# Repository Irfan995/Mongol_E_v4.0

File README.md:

# Mongol_E_v4.0
This is MARS Rover Project of Team Interplanetar from Bangladesh University of Engineering and Technology.

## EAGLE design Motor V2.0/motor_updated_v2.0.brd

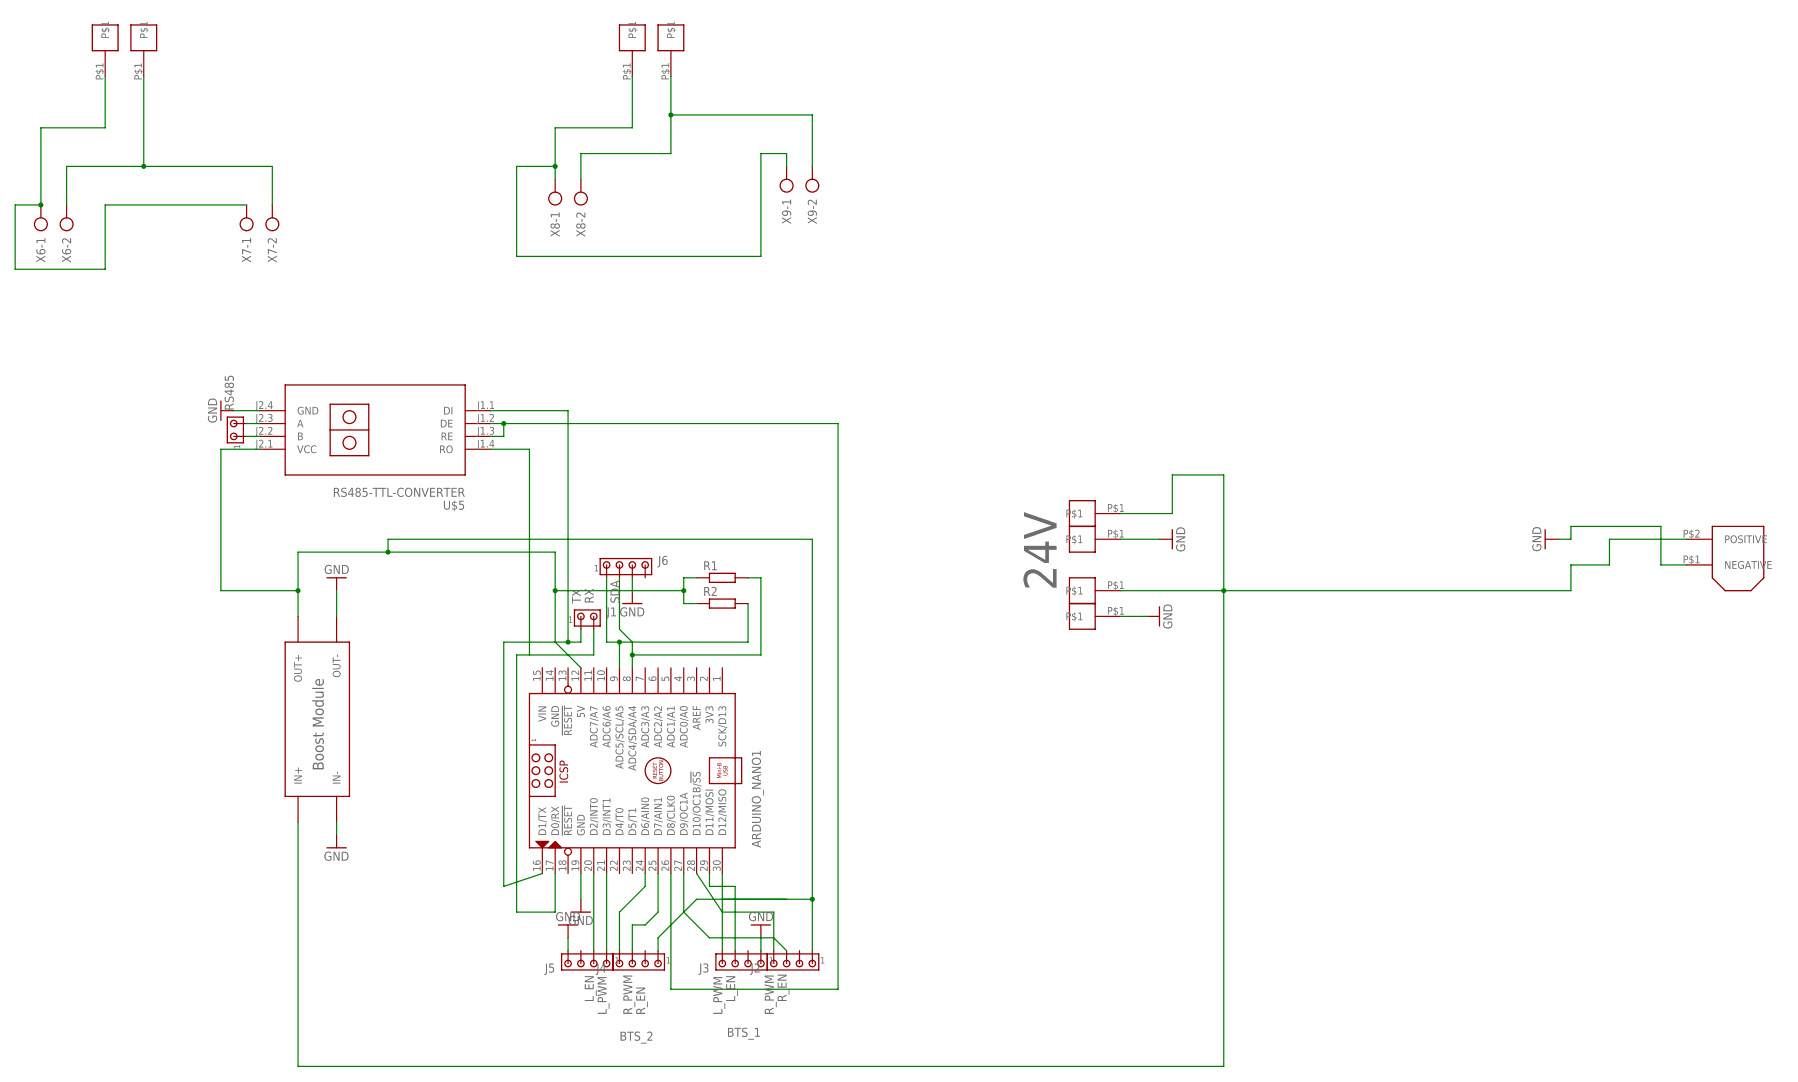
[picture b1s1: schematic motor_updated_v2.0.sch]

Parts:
ARDUINO_NANO1: ARDUINO_NANO
J1: MTA02-100; 10X02MTA
J2, J3, J4, J5, J6: MTA04-100; 10X04MTA
R1, R2: R-EU_0204/7; 0204/7
RS485: MTA02-100; 10X02MTA
U$4: BOOST_MODULE
U$5: RS485-TTL-CONVERTER
U$6, U$8, U$9, U$12, U$13, U$14, U$15, U$23: VIA
U$7: XT60; CONNECTOR
X6, X7, X8, X9: AK300/2

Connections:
GND: ARDUINO_NANO1.14 (GND), ARDUINO_NANO1.19 (GND), J3.1, J5.4, J6.3, U$4.IN-, U$4.OUT-, U$5.J2.4 (GND), U$6.P$1, U$7.P$1 (NEGATIVE), U$9.P$1
unnamed: ARDUINO_NANO1.12 (5V), J2.1, J4.1, R1.1, R2.1, U$4.OUT+, U$5.J2.1 (VCC)
unnamed: ARDUINO_NANO1.9 (ADC5/SCL/A5), J6.1, R2.2
unnamed: ARDUINO_NANO1.20 (D2/INT0), J5.2
unnamed: ARDUINO_NANO1.21 (D3/INT1), J5.1
unnamed: ARDUINO_NANO1.25 (D7/AIN1), J4.3
unnamed: ARDUINO_NANO1.24 (D6/AIN0), J4.4
unnamed: ARDUINO_NANO1.30 (D12/MISO), J3.4
unnamed: ARDUINO_NANO1.26 (D8/CLK0), U$5.J1.2 (DE), U$5.J1.3 (RE)
unnamed: U$4.IN+, U$7.P$2 (POSITIVE), U$8.P$1, U$23.P$1
unnamed: ARDUINO_NANO1.29 (D11/MOSI), J3.3
unnamed: RS485.2, U$5.J2.3 (A)
unnamed: RS485.1, U$5.J2.2 (B)
unnamed: ARDUINO_NANO1.28 (D10/OC1B/!SS), J2.4
unnamed: ARDUINO_NANO1.8 (ADC4/SDA/A4), J6.2, R1.2
unnamed: ARDUINO_NANO1.17 (D0/RX), J1.2, U$5.J1.4 (RO)
unnamed: ARDUINO_NANO1.16 (D1/TX), J1.1, U$5.J1.1 (DI)
unnamed: ARDUINO_NANO1.27 (D9/OC1A), J2.3
unnamed: U$12.P$1, X6.1, X7.1
unnamed: U$14.P$1, X8.1, X9.1
unnamed: U$13.P$1, X6.2, X7.2
unnamed: U$15.P$1, X8.2, X9.2
VIN: ARDUINO_NANO1.15 (VIN)

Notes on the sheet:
SDA
L_PWM
R_PWM
L_EN
R_EN
BTS_1
BTS_2
24V

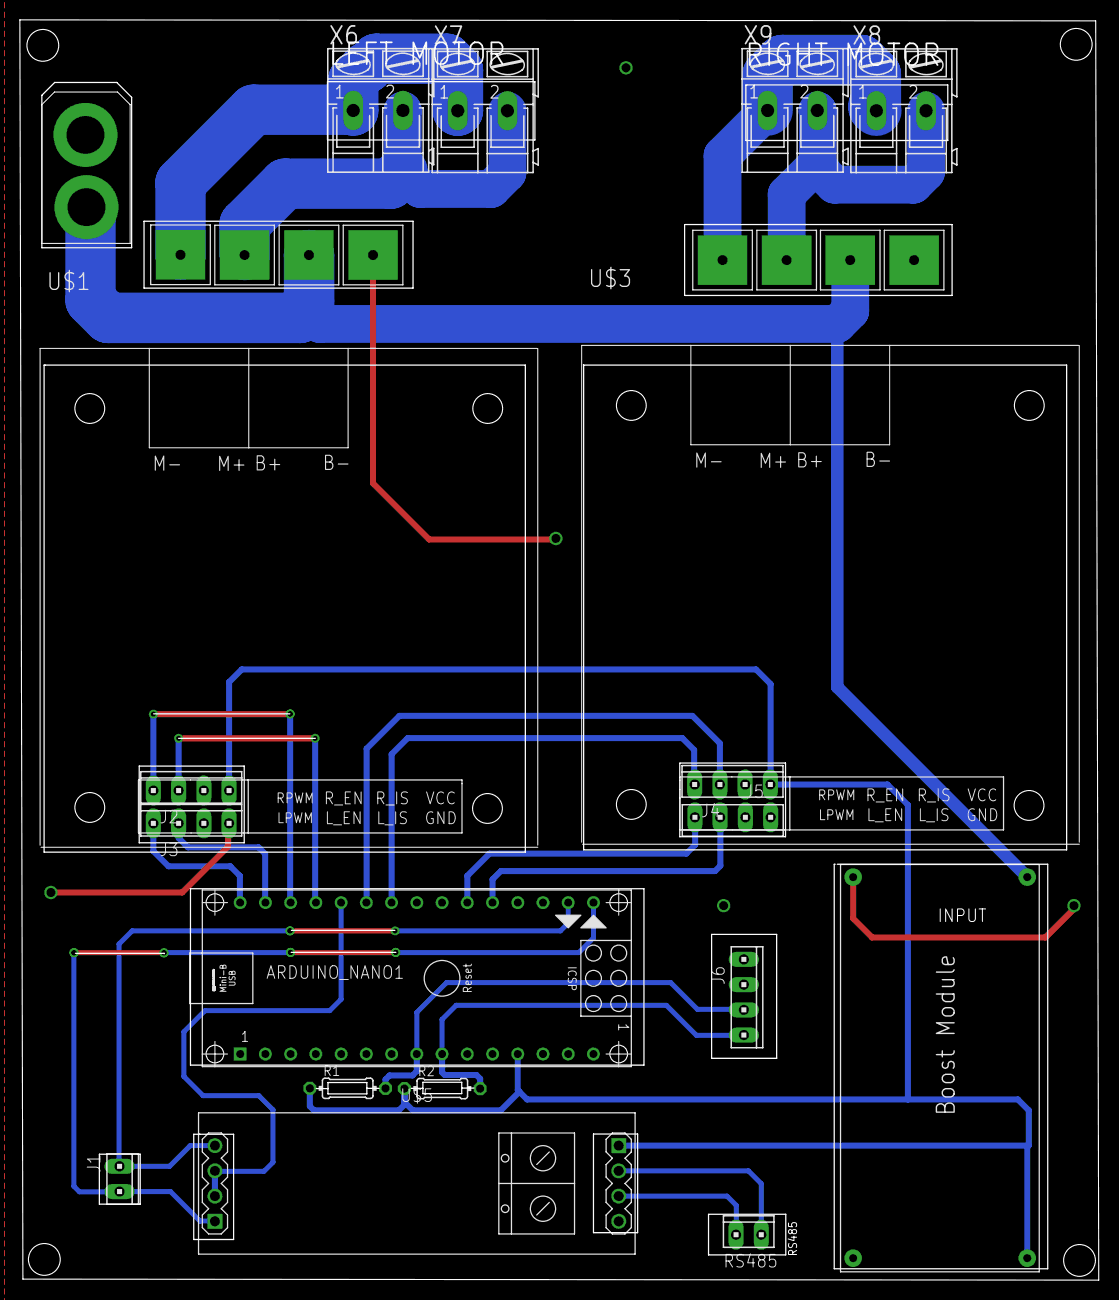
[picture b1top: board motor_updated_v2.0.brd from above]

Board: 2 copper layers, 108.6 x 126.8 mm, 27 parts (0 on the bottom side), 22 nets.

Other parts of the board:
U$1, U$3: IBT-2

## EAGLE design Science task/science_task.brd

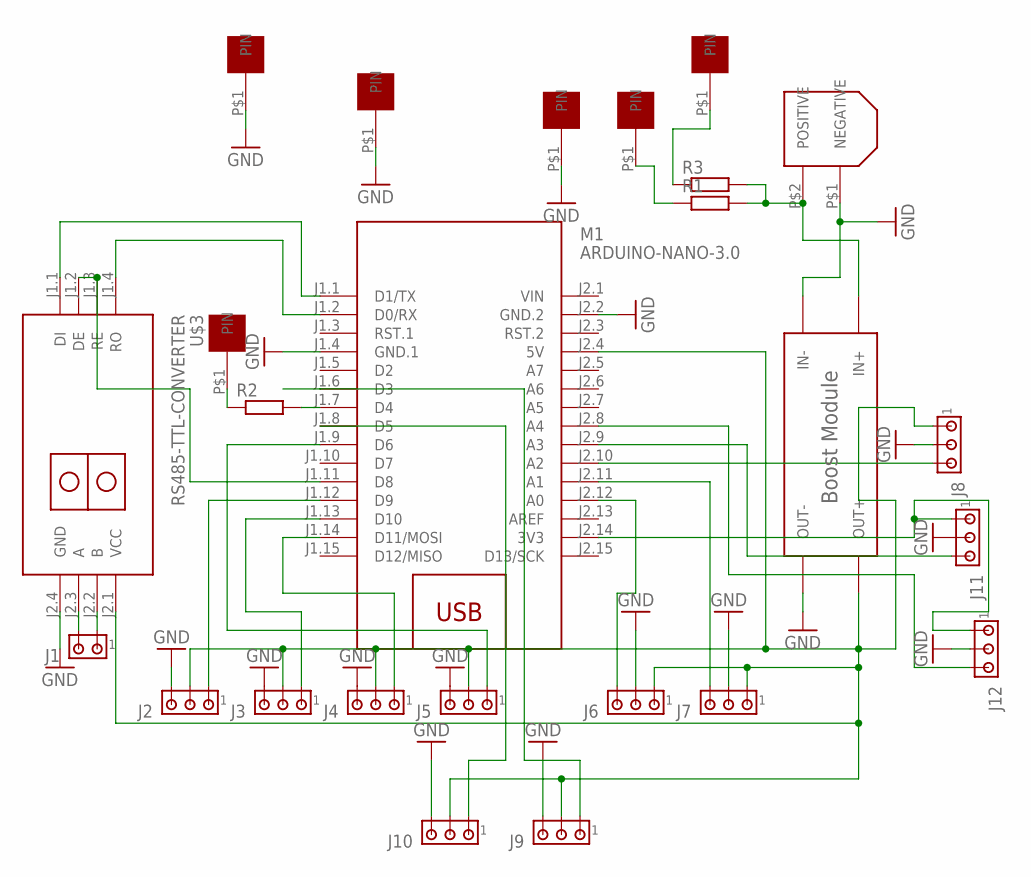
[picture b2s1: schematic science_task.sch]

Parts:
J1: MTA02-100; 10X02MTA
J2, J3, J4, J5, J6, J7, J8, J9, J10, J11, J12: MTA03-100; 10X03MTA
M1: ARDUINO-NANO-3.0
R1, R2, R3: R-EU_0204/7; 0204/7
U$1: XT60; CONNECTOR
U$2: BOOST_MODULE
U$3: RS485-TTL-CONVERTER
U$4, U$5, U$6, U$7, U$8, U$9: VIA

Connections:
GND: J2.3, J3.3, J4.3, J5.3, J6.2, J7.2, J8.2, J9.3, J10.3, J11.2, J12.2, M1.J1.4 (GND.1), M1.J2.2 (GND.2), U$1.P$1 (NEGATIVE), U$2.IN-, U$2.OUT-, U$3.J2.4 (GND), U$5.P$1, U$7.P$1, U$9.P$1
unnamed: R1.2, R3.2, U$1.P$2 (POSITIVE), U$2.IN+
unnamed: J2.2, J3.2, J4.2, J5.2, J6.1, J7.1, J8.1, J9.2, J10.2, M1.J2.4 (5V), U$2.OUT+, U$3.J2.1 (VCC)
unnamed: J2.1, M1.J1.12 (D9)
unnamed: J11.3, M1.J2.9 (A3)
unnamed: J3.1, M1.J1.13 (D10)
unnamed: J1.2, U$3.J2.3 (A)
unnamed: J1.1, U$3.J2.2 (B)
unnamed: M1.J1.2 (D0/RX), U$3.J1.4 (RO)
unnamed: M1.J1.1 (D1/TX), U$3.J1.1 (DI)
unnamed: M1.J1.11 (D8), U$3.J1.2 (DE), U$3.J1.3 (RE)
unnamed: J4.1, M1.J1.14 (D11/MOSI)
unnamed: J5.1, M1.J1.9 (D6)
unnamed: J6.3, M1.J2.12 (A0)
unnamed: J7.3, M1.J2.11 (A1)
unnamed: J8.3, M1.J2.10 (A2)
unnamed: J10.1, M1.J1.8 (D5)
unnamed: J9.1, M1.J1.6 (D3)
unnamed: J12.3, M1.J2.8 (A4)
unnamed: J11.1, J12.1, M1.J2.14 (3V3)
unnamed: M1.J1.7 (D4), R2.2
unnamed: R1.1, U$4.P$1
unnamed: R2.1, U$6.P$1
unnamed: R3.1, U$8.P$1
VIN: M1.J2.1 (VIN)

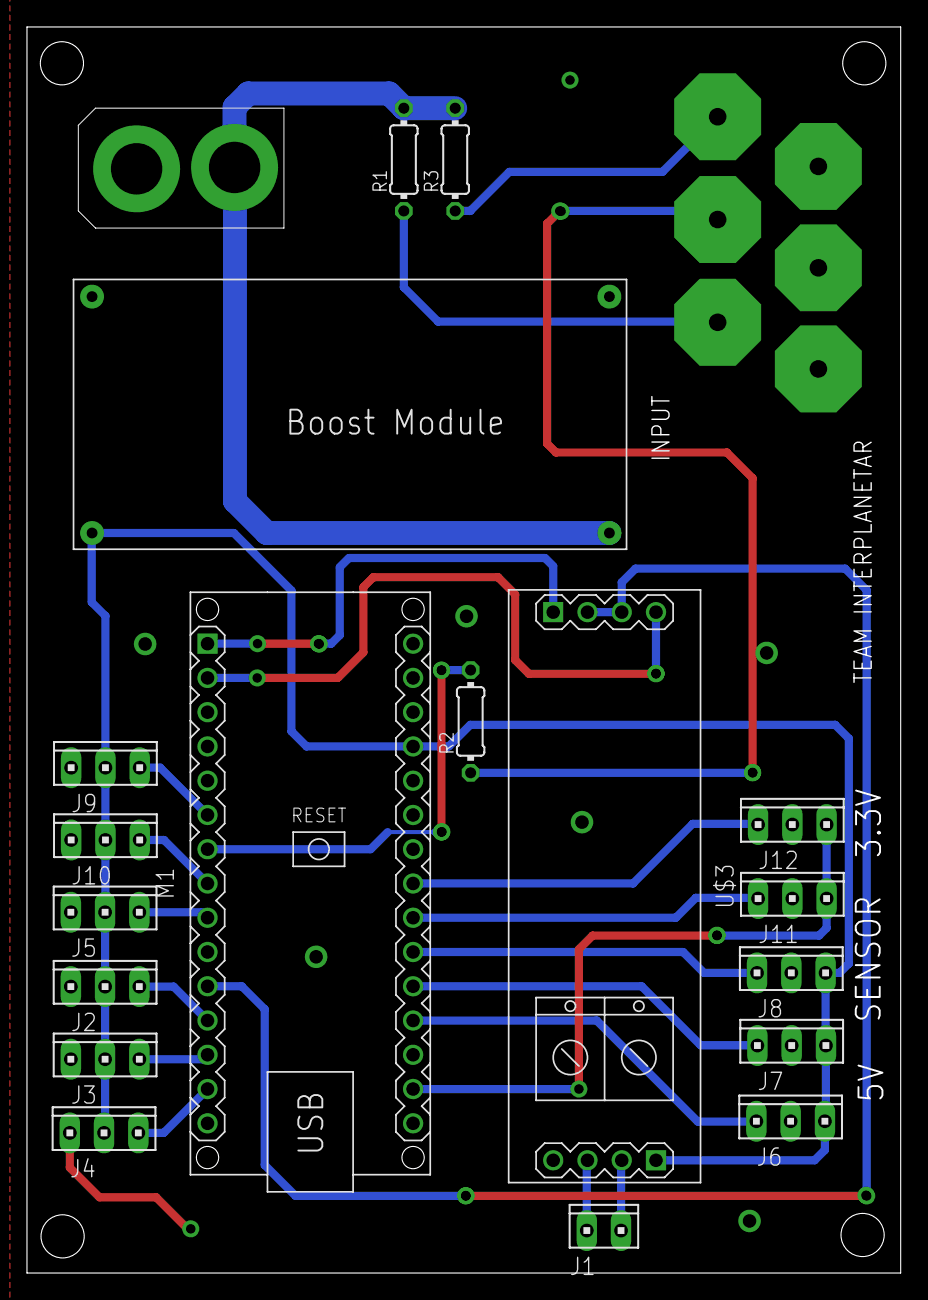
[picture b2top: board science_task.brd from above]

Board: 2 copper layers, 64.8 x 92.4 mm, 25 parts (0 on the bottom side), 24 nets.

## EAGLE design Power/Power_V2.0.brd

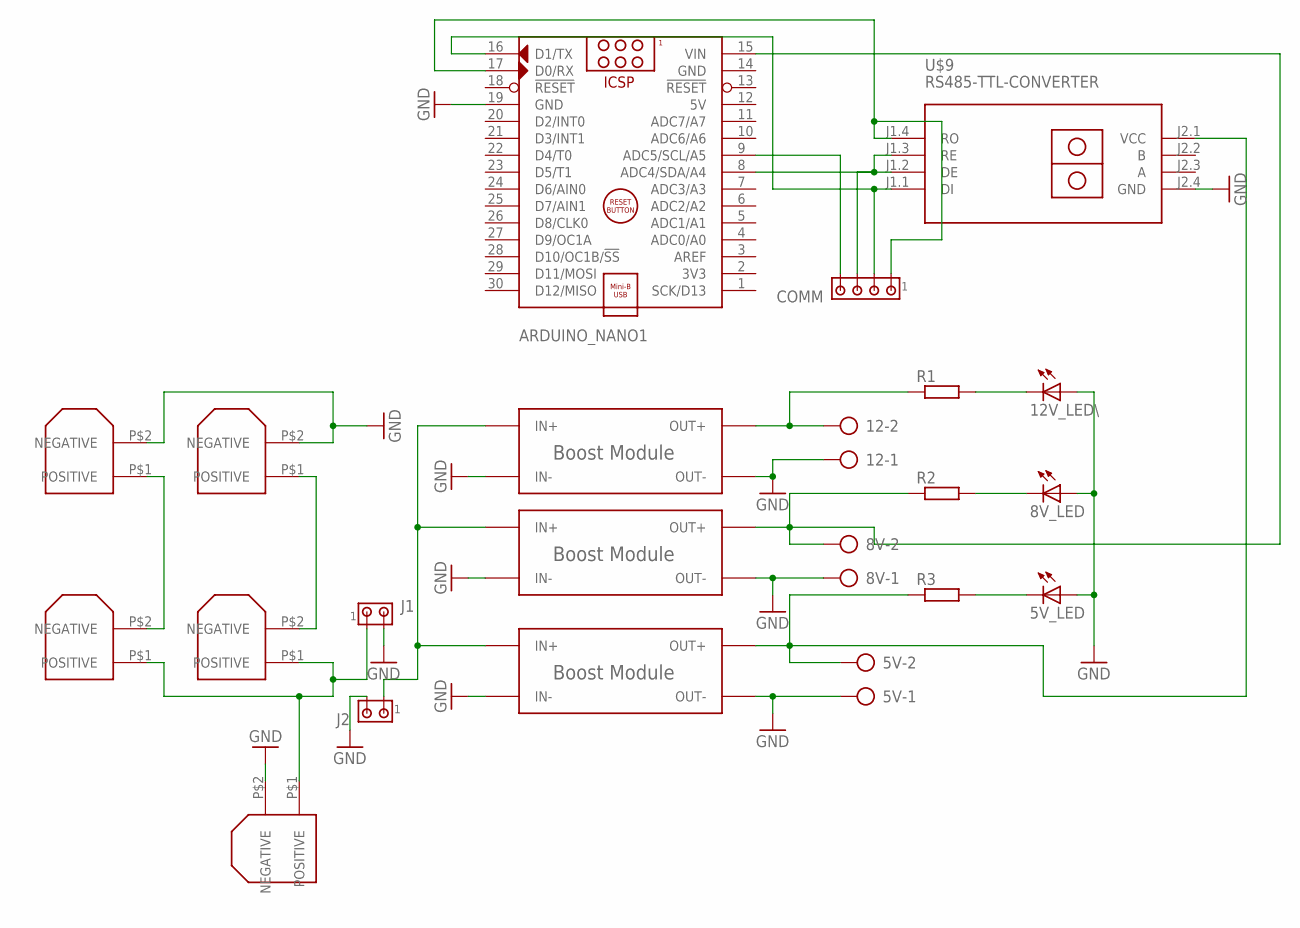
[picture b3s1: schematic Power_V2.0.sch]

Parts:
5V, 8V, 12: AK300/2
5V_LED, 8V_LED, 12V_LED\: LED3MM
ARDUINO_NANO1: ARDUINO_NANO
COMM: MTA04-100; 10X04MTA
J1, J2: MTA02-100; 10X02MTA
R1, R2, R3: R-EU_0204/7; 0204/7
U$1, U$2, U$3, U$4, U$8: XT60; CONNECTOR
U$5, U$6, U$7: BOOST_MODULE
U$9: RS485-TTL-CONVERTER

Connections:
5V: ARDUINO_NANO1.12 (5V)
GND: 5V.1, 5V_LED.A, 8V.1, 8V_LED.A, 12.1, 12V_LED\.A, ARDUINO_NANO1.14 (GND), ARDUINO_NANO1.19 (GND), J1.2, J2.2, U$1.P$2 (NEGATIVE), U$2.P$2 (NEGATIVE), U$5.IN-, U$5.OUT-, U$6.IN-, U$6.OUT-, U$7.IN-, U$7.OUT-, U$8.P$2 (NEGATIVE), U$9.J2.4 (GND)
unnamed: U$2.P$1 (POSITIVE), U$4.P$2 (NEGATIVE)
unnamed: U$1.P$1 (POSITIVE), U$3.P$2 (NEGATIVE)
unnamed: 8V.2, ARDUINO_NANO1.15 (VIN), R2.1, U$5.OUT+
unnamed: J2.1, U$5.IN+, U$6.IN+, U$7.IN+
unnamed: 5V.2, R3.1, U$6.OUT+, U$9.J2.1 (VCC)
unnamed: 12V_LED\.K (C), R1.2
unnamed: 8V_LED.K (C), R2.2
unnamed: 5V_LED.K (C), R3.2
unnamed: ARDUINO_NANO1.9 (ADC5/SCL/A5), COMM.4
unnamed: ARDUINO_NANO1.8 (ADC4/SDA/A4), COMM.3, U$9.J1.2 (DE), U$9.J1.3 (RE)
unnamed: ARDUINO_NANO1.17 (D0/RX), COMM.1, U$9.J1.4 (RO)
unnamed: ARDUINO_NANO1.16 (D1/TX), COMM.2, U$9.J1.1 (DI)
unnamed: J1.1, U$3.P$1 (POSITIVE), U$4.P$1 (POSITIVE), U$8.P$1 (POSITIVE)
unnamed: 12.2, R1.1, U$7.OUT+

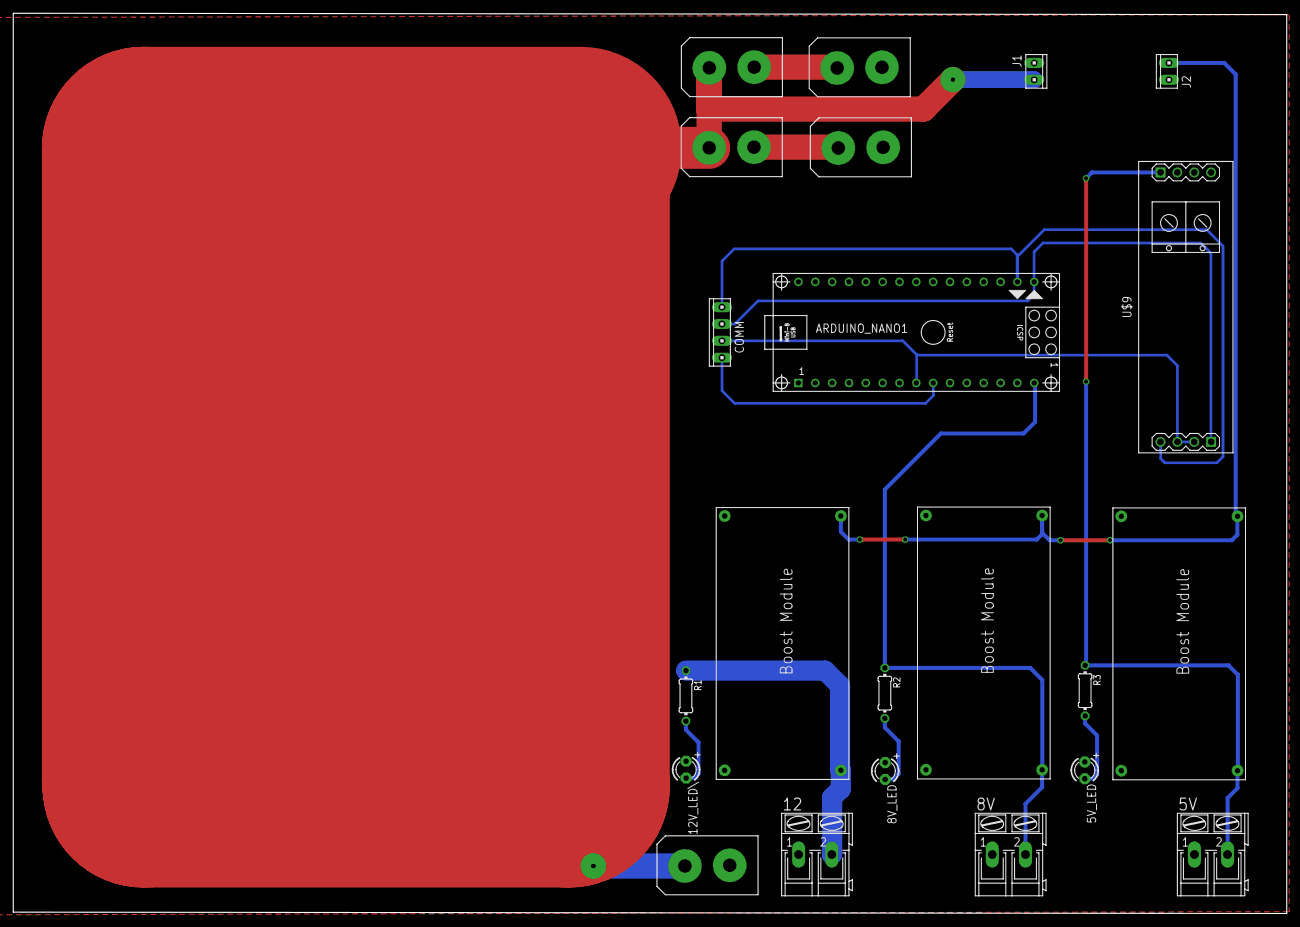
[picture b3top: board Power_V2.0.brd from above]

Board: 2 copper layers, 192.1 x 135.8 mm, 22 parts (0 on the bottom side), 15 nets.

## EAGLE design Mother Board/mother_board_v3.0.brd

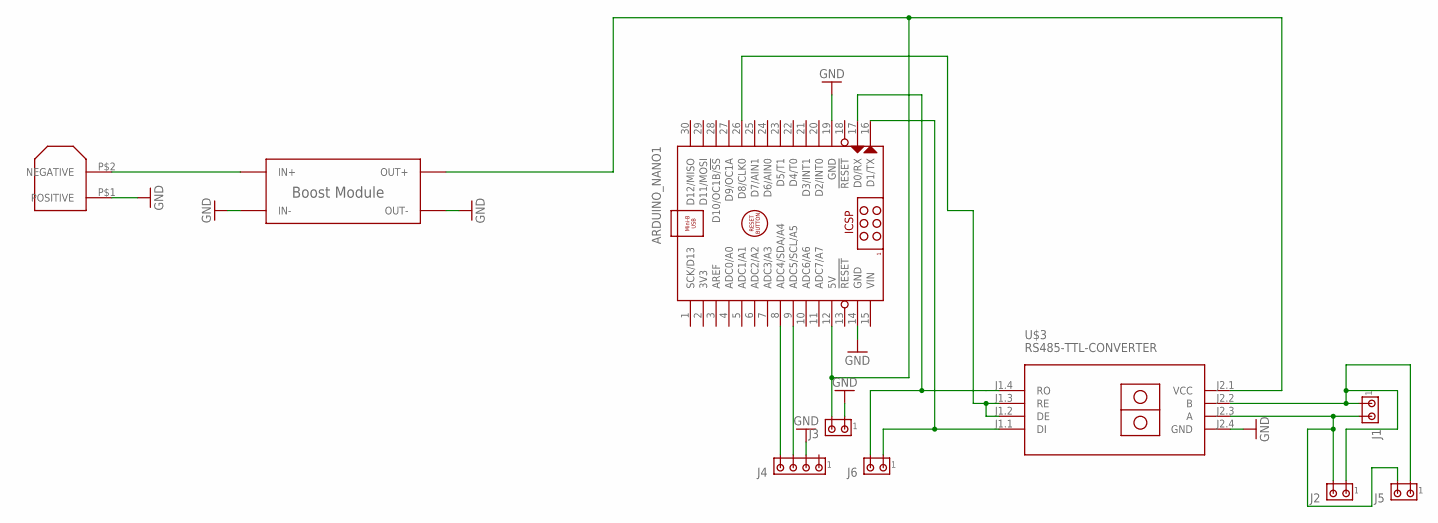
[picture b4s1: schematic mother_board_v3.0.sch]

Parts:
ARDUINO_NANO1: ARDUINO_NANO
J1, J2, J3, J5, J6: MTA02-100; 10X02MTA
J4: MTA04-100; 10X04MTA
U$3: RS485-TTL-CONVERTER
U$5: BOOST_MODULE
U$6: XT60; CONNECTOR

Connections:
GND: ARDUINO_NANO1.14 (GND), ARDUINO_NANO1.19 (GND), J3.1, J4.2, U$3.J2.4 (GND), U$5.IN-, U$5.OUT-, U$6.P$1 (POSITIVE)
unnamed: U$5.IN+, U$6.P$2 (NEGATIVE)
unnamed: J1.2, J2.2, J5.2, U$3.J2.3 (A)
unnamed: J1.1, J2.1, J5.1, U$3.J2.2 (B)
unnamed: ARDUINO_NANO1.26 (D8/CLK0), U$3.J1.2 (DE), U$3.J1.3 (RE)
unnamed: ARDUINO_NANO1.12 (5V), J3.2, U$3.J2.1 (VCC), U$5.OUT+
unnamed: ARDUINO_NANO1.9 (ADC5/SCL/A5), J4.3
unnamed: ARDUINO_NANO1.17 (D0/RX), J6.2
unnamed: ARDUINO_NANO1.8 (ADC4/SDA/A4), J4.4
unnamed: ARDUINO_NANO1.16 (D1/TX), J6.1, U$3.J1.1 (DI)
VIN: ARDUINO_NANO1.15 (VIN)

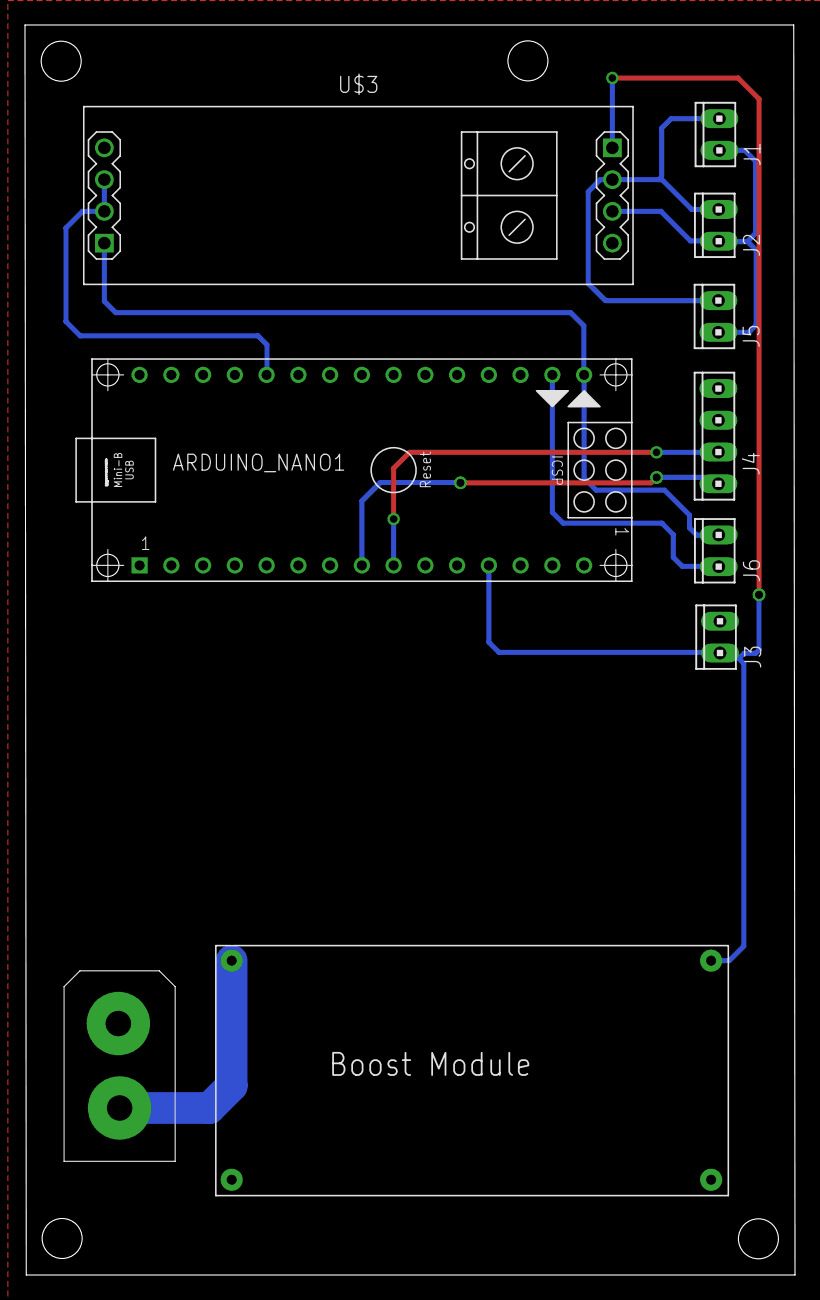
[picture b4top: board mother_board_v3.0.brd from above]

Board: 2 copper layers, 61.6 x 100.0 mm, 10 parts (0 on the bottom side), 10 nets.

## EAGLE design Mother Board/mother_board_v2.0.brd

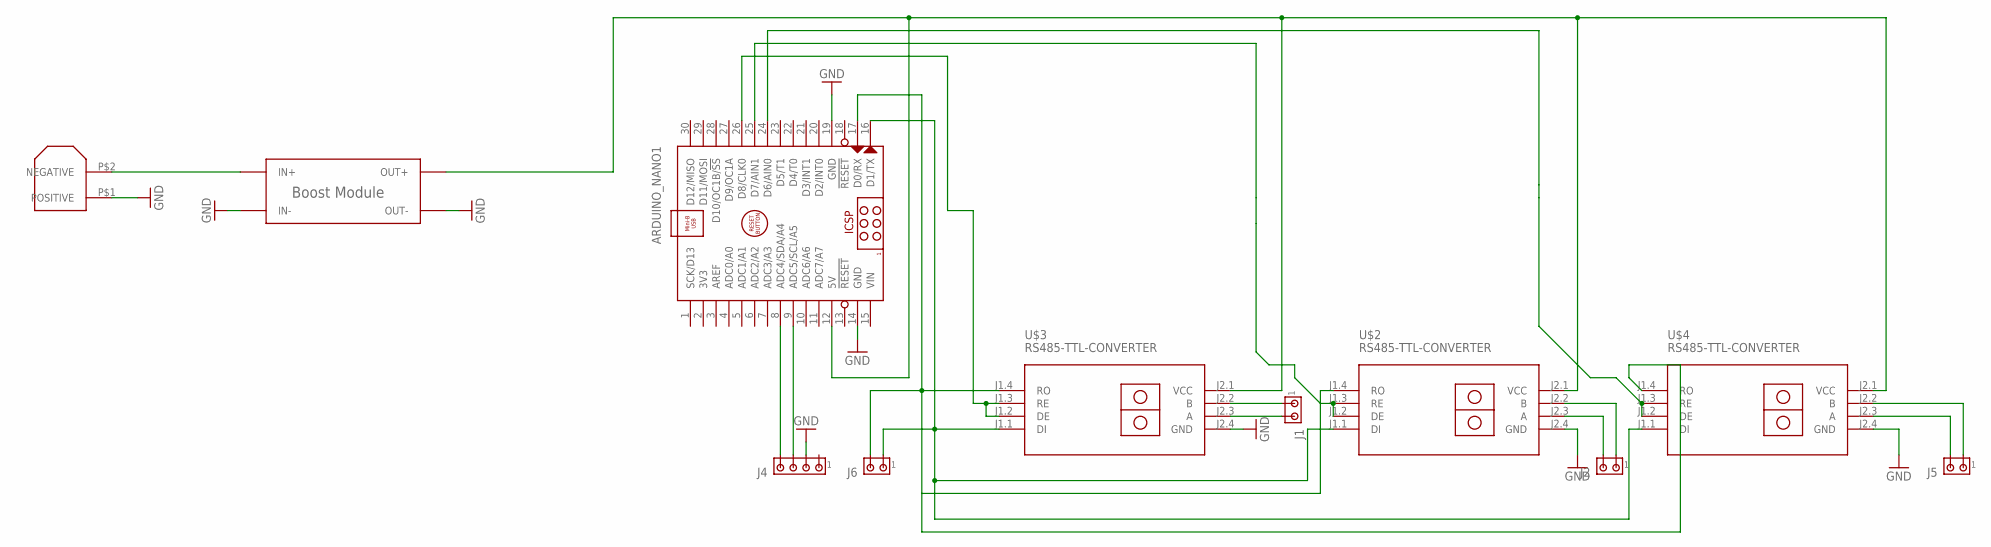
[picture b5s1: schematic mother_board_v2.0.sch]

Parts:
ARDUINO_NANO1: ARDUINO_NANO
J1, J2, J5, J6: MTA02-100; 10X02MTA
J4: MTA04-100; 10X04MTA
U$2, U$3, U$4: RS485-TTL-CONVERTER
U$5: BOOST_MODULE
U$6: XT60; CONNECTOR

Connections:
GND: ARDUINO_NANO1.14 (GND), ARDUINO_NANO1.19 (GND), J4.2, U$2.J2.4 (GND), U$3.J2.4 (GND), U$4.J2.4 (GND), U$5.IN-, U$5.OUT-, U$6.P$1 (POSITIVE)
unnamed: J5.2, U$4.J2.3 (A)
unnamed: J5.1, U$4.J2.2 (B)
unnamed: J2.2, U$2.J2.3 (A)
unnamed: J1.2, U$3.J2.3 (A)
unnamed: J1.1, U$3.J2.2 (B)
unnamed: ARDUINO_NANO1.26 (D8/CLK0), U$3.J1.2 (DE), U$3.J1.3 (RE)
unnamed: ARDUINO_NANO1.12 (5V), U$2.J2.1 (VCC), U$3.J2.1 (VCC), U$4.J2.1 (VCC), U$5.OUT+
unnamed: U$5.IN+, U$6.P$2 (NEGATIVE)
unnamed: J2.1, U$2.J2.2 (B)
unnamed: ARDUINO_NANO1.25 (D7/AIN1), U$2.J1.2 (DE), U$2.J1.3 (RE)
unnamed: ARDUINO_NANO1.9 (ADC5/SCL/A5), J4.3
unnamed: ARDUINO_NANO1.17 (D0/RX), J6.2, U$2.J1.4 (RO), U$3.J1.4 (RO), U$4.J1.4 (RO)
unnamed: ARDUINO_NANO1.8 (ADC4/SDA/A4), J4.4
unnamed: ARDUINO_NANO1.24 (D6/AIN0), U$4.J1.2 (DE), U$4.J1.3 (RE)
unnamed: ARDUINO_NANO1.16 (D1/TX), J6.1, U$2.J1.1 (DI), U$3.J1.1 (DI), U$4.J1.1 (DI)
VIN: ARDUINO_NANO1.15 (VIN)

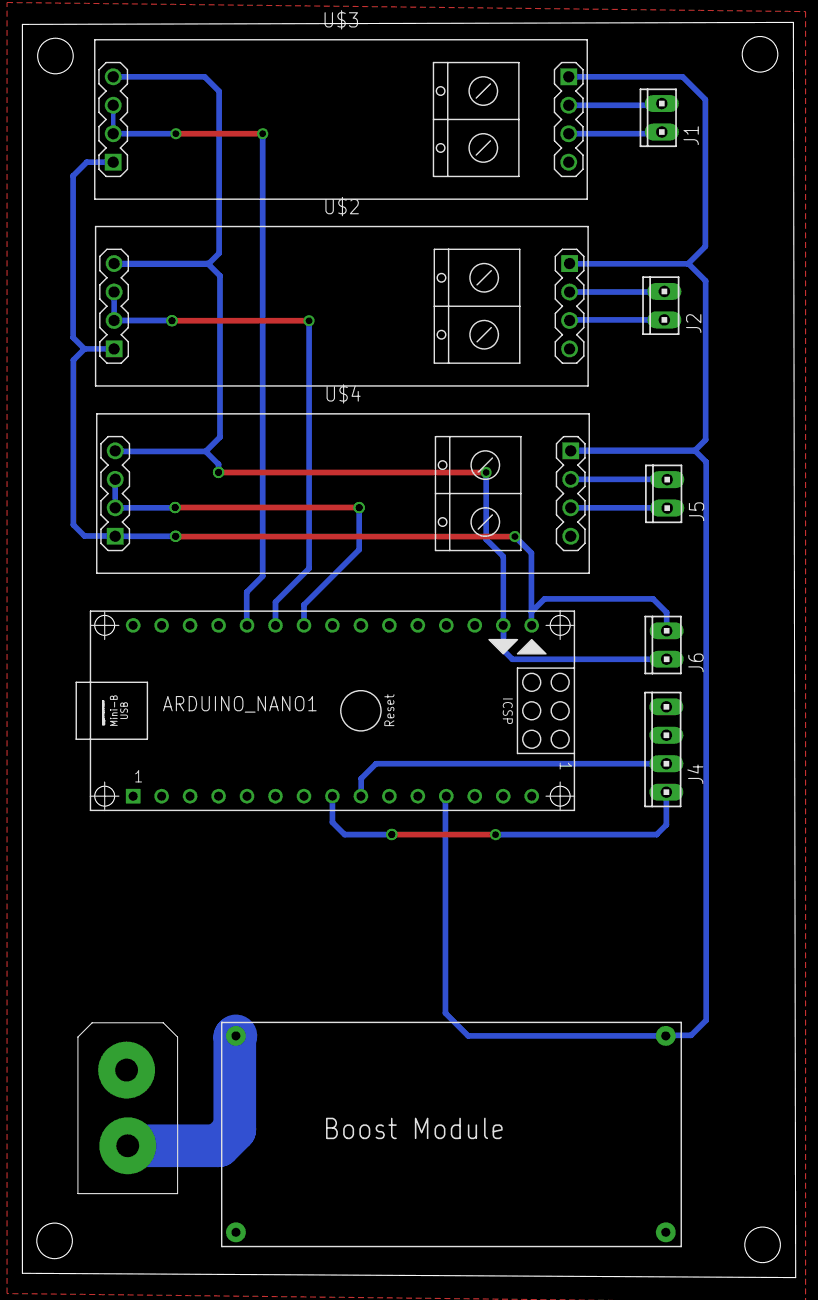
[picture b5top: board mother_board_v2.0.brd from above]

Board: 2 copper layers, 69.0 x 112.0 mm, 11 parts (0 on the bottom side), 16 nets.

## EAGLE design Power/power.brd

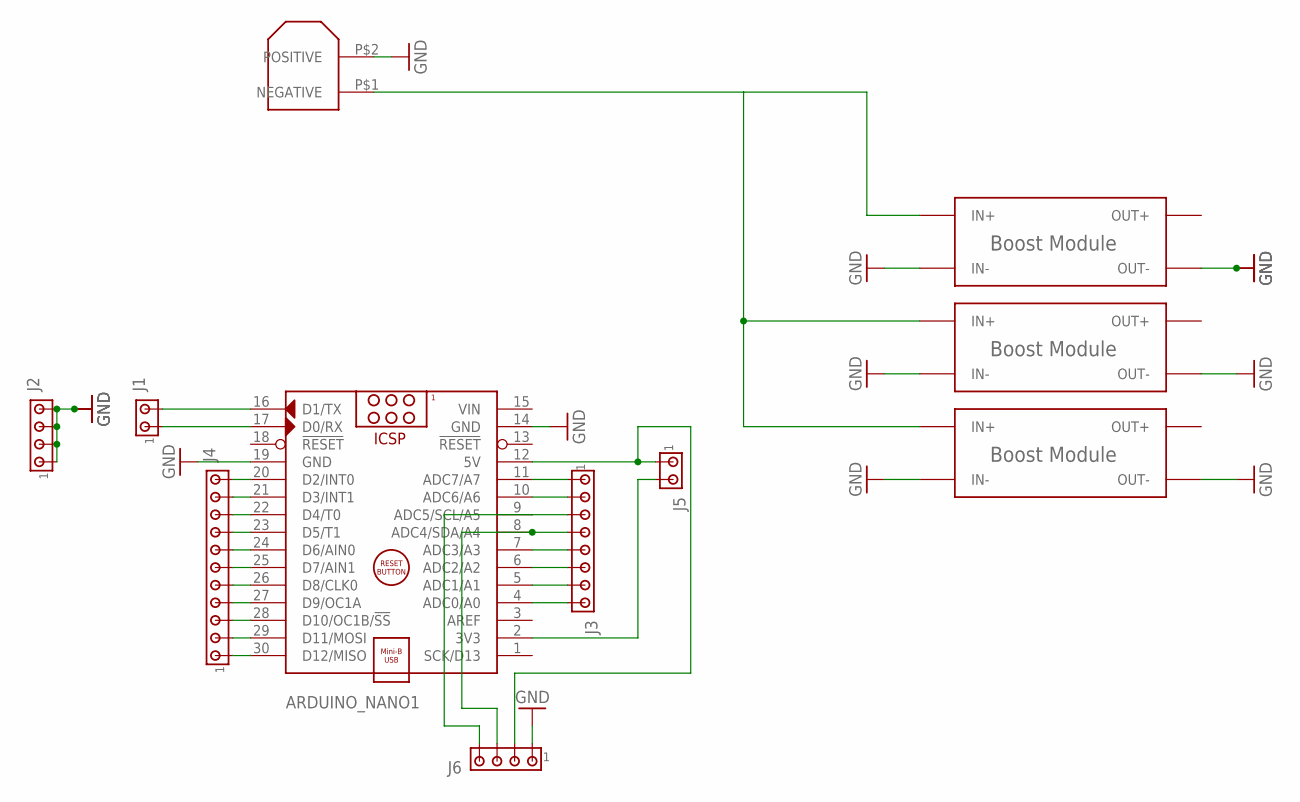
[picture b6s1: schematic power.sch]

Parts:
ARDUINO_NANO1: ARDUINO_NANO
J1, J5: MTA02-100; 10X02MTA
J2, J6: MTA04-100; 10X04MTA
J3: MTA08-100; 10X08MTA
J4: MTA11-156; 1X11MTA
U$1, U$2, U$3: BOOST_MODULE
U$4: XT60; CONNECTOR

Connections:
GND: ARDUINO_NANO1.14 (GND), ARDUINO_NANO1.19 (GND), J2.1, J2.2, J2.3, J2.4, J6.1, U$1.IN-, U$1.OUT-, U$2.IN-, U$2.OUT-, U$3.IN-, U$3.OUT-, U$4.P$2 (POSITIVE)
unnamed: U$1.IN+, U$2.IN+, U$3.IN+, U$4.P$1 (NEGATIVE)
unnamed: ARDUINO_NANO1.16 (D1/TX), J1.2
unnamed: ARDUINO_NANO1.17 (D0/RX), J1.1
unnamed: ARDUINO_NANO1.20 (D2/INT0), J4.11
unnamed: ARDUINO_NANO1.21 (D3/INT1), J4.10
unnamed: ARDUINO_NANO1.22 (D4/T0), J4.9
unnamed: ARDUINO_NANO1.23 (D5/T1), J4.8
unnamed: ARDUINO_NANO1.24 (D6/AIN0), J4.7
unnamed: ARDUINO_NANO1.25 (D7/AIN1), J4.6
unnamed: ARDUINO_NANO1.26 (D8/CLK0), J4.5
unnamed: ARDUINO_NANO1.27 (D9/OC1A), J4.4
unnamed: ARDUINO_NANO1.28 (D10/OC1B/!SS), J4.3
unnamed: ARDUINO_NANO1.29 (D11/MOSI), J4.2
unnamed: ARDUINO_NANO1.30 (D12/MISO), J4.1
unnamed: ARDUINO_NANO1.11 (ADC7/A7), J3.1
unnamed: ARDUINO_NANO1.10 (ADC6/A6), J3.2
unnamed: ARDUINO_NANO1.9 (ADC5/SCL/A5), J3.3, J6.4
unnamed: ARDUINO_NANO1.8 (ADC4/SDA/A4), J3.4, J6.3
unnamed: ARDUINO_NANO1.7 (ADC3/A3), J3.5
unnamed: ARDUINO_NANO1.6 (ADC2/A2), J3.6
unnamed: ARDUINO_NANO1.5 (ADC1/A1), J3.7
unnamed: ARDUINO_NANO1.4 (ADC0/A0), J3.8
unnamed: ARDUINO_NANO1.12 (5V), J5.1, J6.2
unnamed: ARDUINO_NANO1.2 (3V3), J5.2
VIN: ARDUINO_NANO1.15 (VIN)

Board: 2 copper layers, 11 parts (0 on the bottom side), 25 nets, no tracks yet.

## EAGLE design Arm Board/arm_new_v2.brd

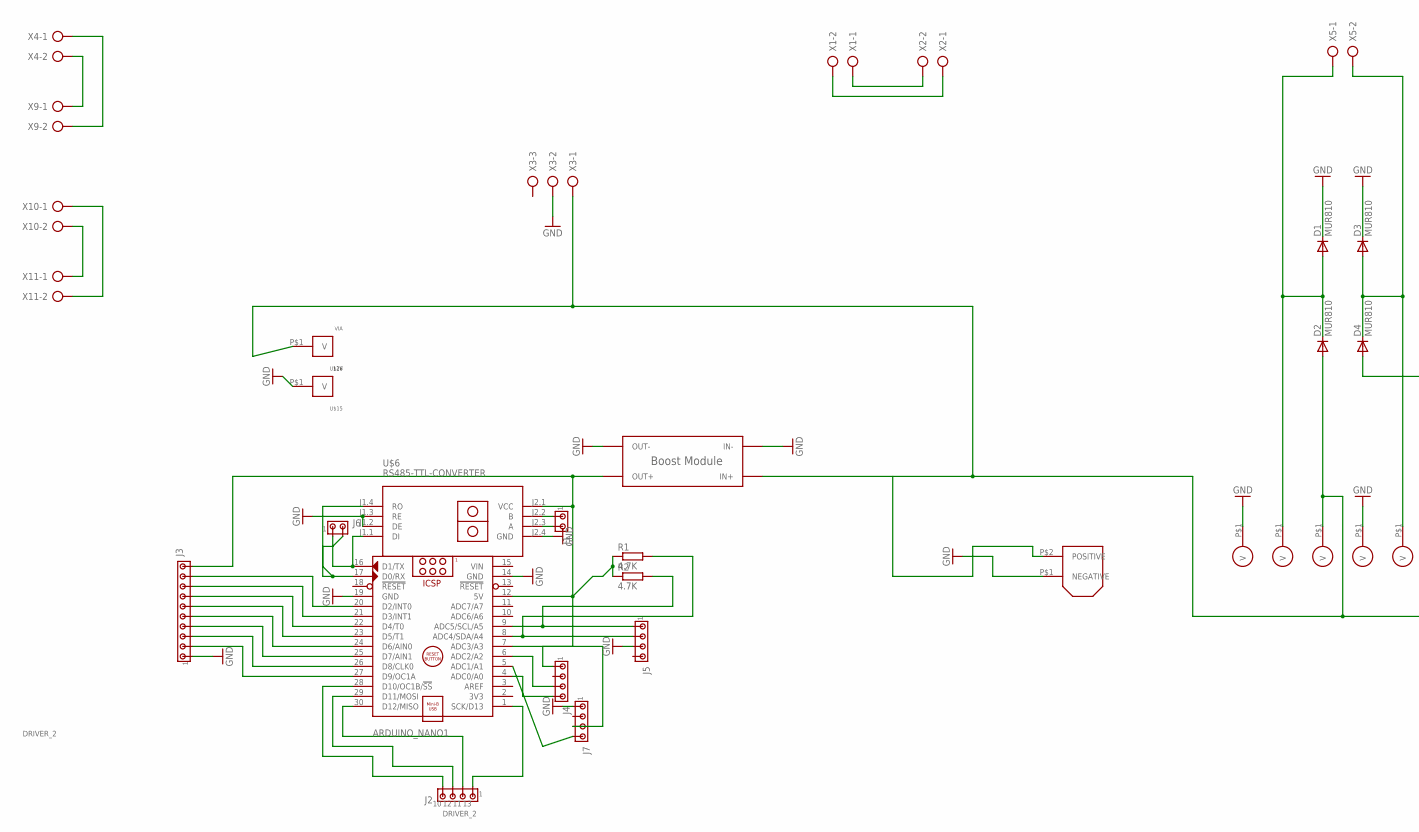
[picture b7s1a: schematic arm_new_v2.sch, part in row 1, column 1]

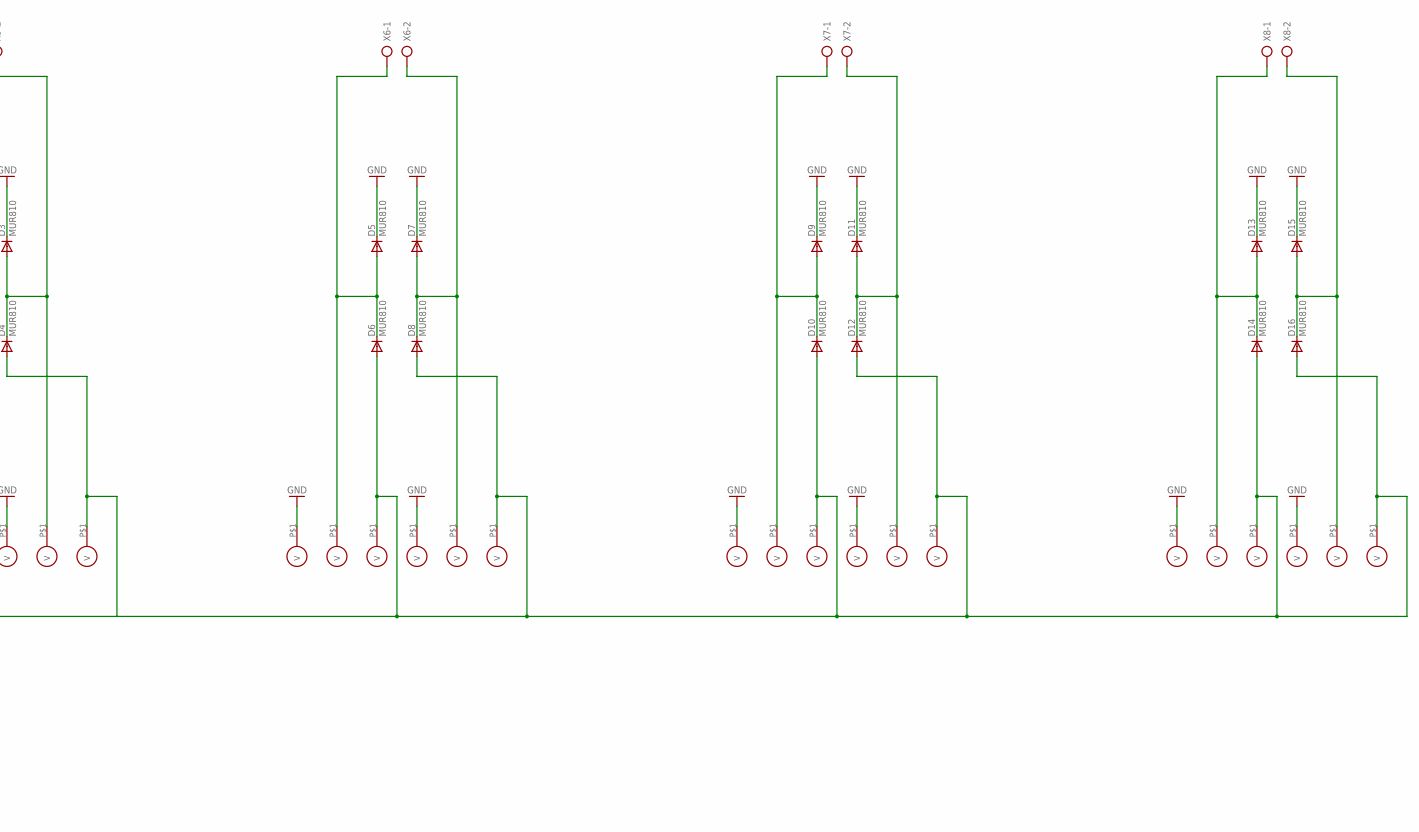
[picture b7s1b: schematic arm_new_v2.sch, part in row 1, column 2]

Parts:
ARDUINO_NANO1: ARDUINO_NANO
D1, D2, D3, D4, D5, D6, D7, D8, D9, D10, D11, D12, D13, D14, D15, D16: MUR810; TO220ACS
J1, J6: MTA02-100; 10X02MTA
J2, J4, J5, J7: MTA04-100; 10X04MTA
J3: MTA10-100; 10X10MTA
NO, NO1, NO2, NO3: NO; ROUND_VIA
R1, R2: 4.7K; 0204/7
U$1: BOOST_MODULE
U$4: XT60; CONNECTOR
U$6: RS485-TTL-CONVERTER
U$15: 12V; VIA
U$16: VIA
U$17, U$18, U$19, U$20, U$21, U$22, U$23, U$24, U$25, U$26, U$27, U$28, U$29, U$30, U$31, U$32, U$33, U$34, U$35, U$36: ROUND_VIA
X1, X2, X4, X5, X6, X7, X8, X9, X10, X11: AK300/2
X3: AK300/3

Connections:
5V: ARDUINO_NANO1.12 (5V), J3.10, J4.1, R1.1, R2.1, U$1.OUT+, U$6.J2.1 (VCC)
GND: ARDUINO_NANO1.14 (GND), ARDUINO_NANO1.19 (GND), D1.C, D3.C, D5.C, D7.C, D9.C, D11.C, D13.C, D15.C, J3.1, J5.3, J7.1, NO.P$1, NO1.P$1, NO2.P$1, NO3.P$1, U$1.IN-, U$1.OUT-, U$4.P$1 (NEGATIVE), U$6.J1.2 (DE), U$6.J1.3 (RE), U$6.J2.4 (GND), U$15.P$1, U$20.P$1, U$24.P$1, U$29.P$1, U$34.P$1, X3.2
unnamed: ARDUINO_NANO1.6 (ADC2/A2), J4.3
unnamed: ARDUINO_NANO1.4 (ADC0/A0), J4.4
unnamed: ARDUINO_NANO1.7 (ADC3/A3), J7.3
unnamed: ARDUINO_NANO1.5 (ADC1/A1), J7.4
unnamed: D2.A, D4.A, D6.A, D8.A, D10.A, D12.A, D14.A, D16.A, U$1.IN+, U$4.P$2 (POSITIVE), U$16.P$1, U$19.P$1, U$22.P$1, U$23.P$1, U$26.P$1, U$28.P$1, U$31.P$1, U$33.P$1, U$36.P$1, X3.1
unnamed: X4.2, X9.1
unnamed: X4.1, X9.2
unnamed: X10.2, X11.1
unnamed: ARDUINO_NANO1.1 (SCK/D13), J2.1
unnamed: D1.A, D2.C, U$18.P$1, X5.1
unnamed: ARDUINO_NANO1.30 (D12/MISO), J2.2
unnamed: ARDUINO_NANO1.20 (D2/INT0), J3.9
unnamed: ARDUINO_NANO1.29 (D11/MOSI), J2.3
unnamed: ARDUINO_NANO1.28 (D10/OC1B/!SS), J2.4
unnamed: ARDUINO_NANO1.21 (D3/INT1), J3.8
unnamed: ARDUINO_NANO1.22 (D4/T0), J3.7
unnamed: D5.A, D6.C, U$17.P$1, X6.1
unnamed: ARDUINO_NANO1.23 (D5/T1), J3.6
unnamed: ARDUINO_NANO1.24 (D6/AIN0), J3.5
unnamed: ARDUINO_NANO1.25 (D7/AIN1), J3.4
unnamed: ARDUINO_NANO1.26 (D8/CLK0), J3.3
unnamed: ARDUINO_NANO1.27 (D9/OC1A), J3.2
unnamed: ARDUINO_NANO1.16 (D1/TX), J6.1, U$6.J1.1 (DI)
unnamed: J1.1, U$6.J2.2 (B)
unnamed: ARDUINO_NANO1.9 (ADC5/SCL/A5), J5.1, R2.2
unnamed: ARDUINO_NANO1.8 (ADC4/SDA/A4), J5.2, R1.2
unnamed: D9.A, D10.C, U$27.P$1, X7.1
unnamed: D3.A, D4.C, U$21.P$1, X5.2
unnamed: D7.A, D8.C, U$25.P$1, X6.2
unnamed: D13.A, D14.C, U$32.P$1, X8.1
unnamed: D11.A, D12.C, U$30.P$1, X7.2
unnamed: X10.1, X11.2
unnamed: D15.A, D16.C, U$35.P$1, X8.2
unnamed: X1.1, X2.2
unnamed: ARDUINO_NANO1.17 (D0/RX), J6.2, U$6.J1.4 (RO)
unnamed: J1.2, U$6.J2.3 (A)
unnamed: X1.2, X2.1
VIN: ARDUINO_NANO1.15 (VIN)

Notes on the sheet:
DRIVER_2

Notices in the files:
parts and their libraries:
diy-modules: Released under the Creative Commons Attribution 4.0 International License: http://creativecommons.org/licenses/by/4.0
